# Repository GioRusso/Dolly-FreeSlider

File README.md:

# Dolly Free-Slider

Proyecto de grado - Ingeniería electrónica

Universidad del Norte - Barranquilla, Colombia

## Autores
* **Daniela Rada Estarita** - *Estudiante de pregrado* - destarita@uninorte.edu.co
* **Giorgio Russo Munarriz** - *Estudiante de pregrado* - grusso@uninorte.edu.co
* **Winston Percybrooks, Ph.D., M.Sc.** - *Ingeniero, asesor* - wpercyb@uninorte.edu.co
* **Norelli Schettini, Ph.D., M.Sc.** - *Ingeniera, asesora* - nschettini@uninorte.edu.co
* **Mauricio García, Magister** - *Diseñador Grafico, asesor* - garciamauricio@uninorte.edu.co

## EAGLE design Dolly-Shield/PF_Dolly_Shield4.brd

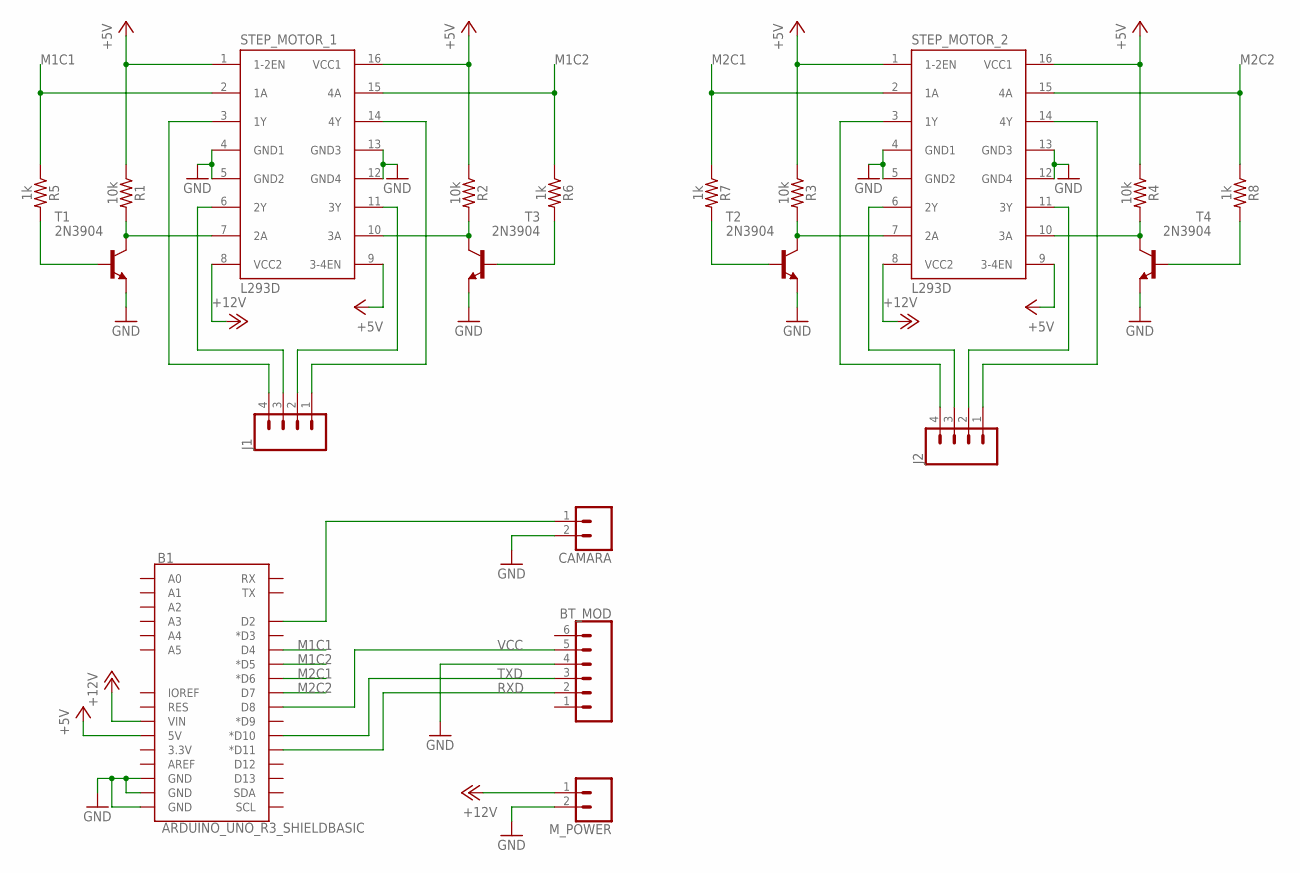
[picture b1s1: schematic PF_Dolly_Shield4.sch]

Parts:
B1: ARDUINO_UNO_R3_SHIELDBASIC; UNO_R3_SHIELD
BT_MOD: CONN_06LONGPADS; 1X06_LONGPADS
CAMARA: CONN_025MM; SCREWTERMINAL-5MM-2
J1, J2: CONN_04POLAR; MOLEX-1X4
M_POWER: CONN_025MM; SCREWTERMINAL-5MM-2
R1, R2, R3, R4: 10k; AXIAL-0.3
R5, R6, R7, R8: 1k; AXIAL-0.3
STEP_MOTOR_1, STEP_MOTOR_2: L293D; DIL16
T1, T2, T3, T4: 2N3904; TO92

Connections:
+5V: B1.5V, R1.P$1 (1), R2.P$1 (1), R3.P$1 (1), R4.P$1 (1), STEP_MOTOR_1.1 (1-2EN), STEP_MOTOR_1.9 (3-4EN), STEP_MOTOR_1.16 (VCC1), STEP_MOTOR_2.1 (1-2EN), STEP_MOTOR_2.9 (3-4EN), STEP_MOTOR_2.16 (VCC1)
+12V: B1.VIN, M_POWER.1, STEP_MOTOR_1.8 (VCC2), STEP_MOTOR_2.8 (VCC2)
GND: B1.GND@0 (GND), B1.GND@1 (GND), B1.GND@2 (GND), BT_MOD.4, CAMARA.2, M_POWER.2, STEP_MOTOR_1.4 (GND1), STEP_MOTOR_1.5 (GND2), STEP_MOTOR_1.12 (GND4), STEP_MOTOR_1.13 (GND3), STEP_MOTOR_2.4 (GND1), STEP_MOTOR_2.5 (GND2), STEP_MOTOR_2.12 (GND4), STEP_MOTOR_2.13 (GND3), T1.3 (E), T2.3 (E), T3.3 (E), T4.3 (E)
M1C1: B1.D4, R5.P$1 (1), STEP_MOTOR_1.2 (1A)
M1C2: B1.D5 (*D5), R6.P$1 (1), STEP_MOTOR_1.15 (4A)
M2C1: B1.D6 (*D6), R7.P$1 (1), STEP_MOTOR_2.2 (1A)
M2C2: B1.D7, R8.P$1 (1), STEP_MOTOR_2.15 (4A)
unnamed: J1.4, STEP_MOTOR_1.3 (1Y)
unnamed: J1.3, STEP_MOTOR_1.6 (2Y)
unnamed: J1.2, STEP_MOTOR_1.11 (3Y)
unnamed: J1.1, STEP_MOTOR_1.14 (4Y)
unnamed: J2.3, STEP_MOTOR_2.6 (2Y)
unnamed: J2.2, STEP_MOTOR_2.11 (3Y)
unnamed: J2.4, STEP_MOTOR_2.3 (1Y)
unnamed: J2.1, STEP_MOTOR_2.14 (4Y)
unnamed: R1.P$2 (2), STEP_MOTOR_1.7 (2A), T1.1 (C)
unnamed: R2.P$2 (2), STEP_MOTOR_1.10 (3A), T3.1 (C)
unnamed: R3.P$2 (2), STEP_MOTOR_2.7 (2A), T2.1 (C)
unnamed: R4.P$2 (2), STEP_MOTOR_2.10 (3A), T4.1 (C)
unnamed: R5.P$2 (2), T1.2 (B)
unnamed: R6.P$2 (2), T3.2 (B)
unnamed: R7.P$2 (2), T2.2 (B)
unnamed: R8.P$2 (2), T4.2 (B)
unnamed: B1.D2, CAMARA.1
RXD: B1.D11 (*D11), BT_MOD.2
TXD: B1.D10 (*D10), BT_MOD.3
VCC: B1.D8, BT_MOD.5

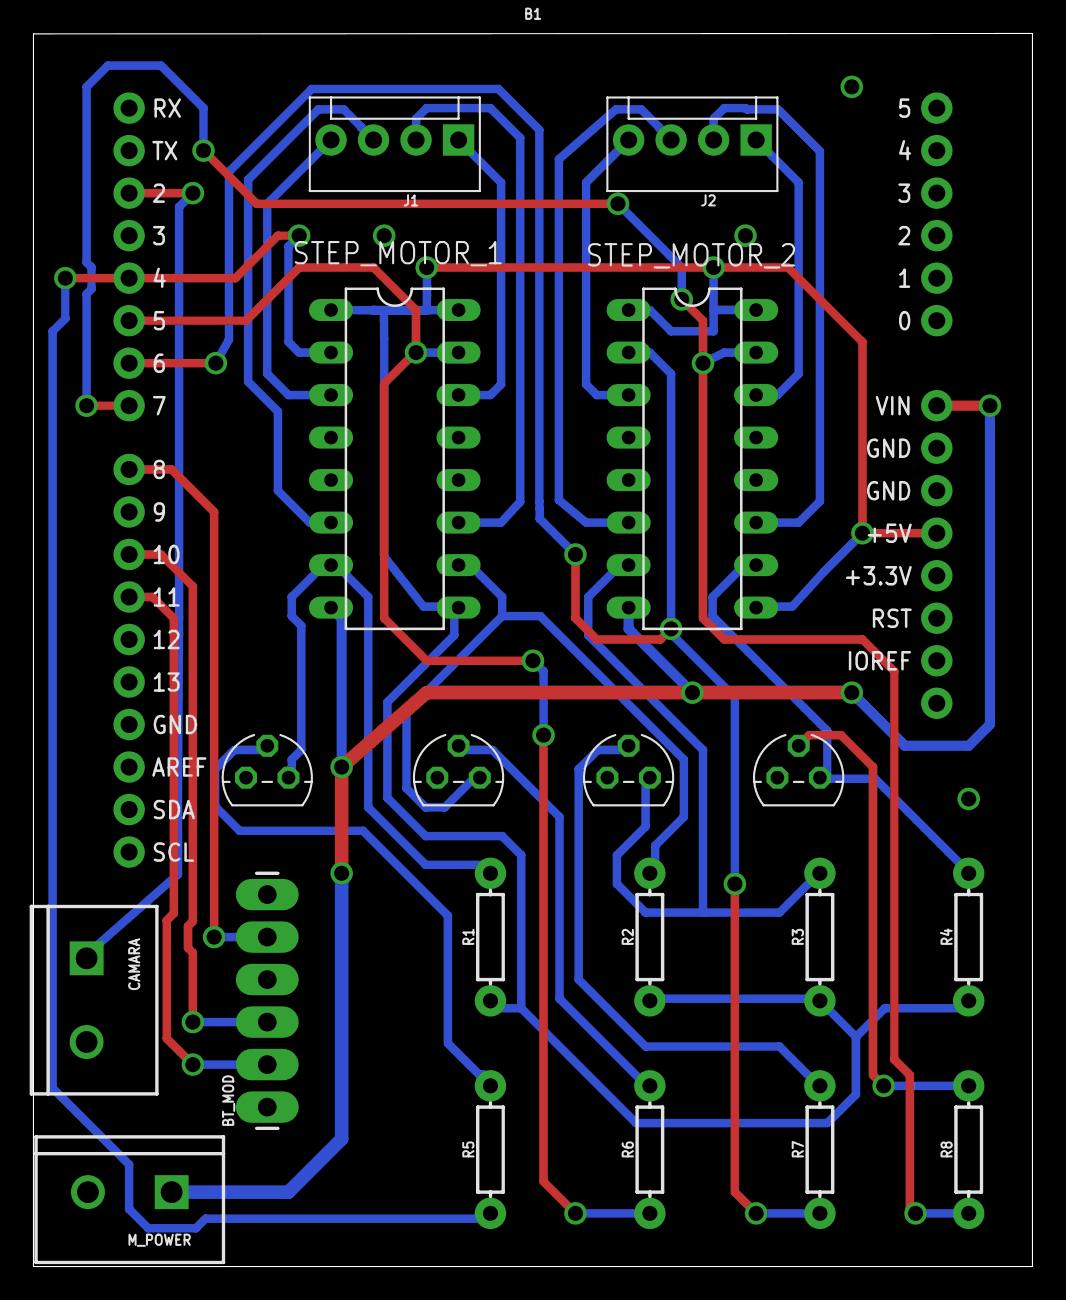
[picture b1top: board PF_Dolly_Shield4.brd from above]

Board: 2 copper layers, 59.7 x 73.7 mm, 20 parts (0 on the bottom side), 27 nets.

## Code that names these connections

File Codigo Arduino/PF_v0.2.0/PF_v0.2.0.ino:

#include <Stepper.h>

#define motorSteps 200
#define M1C1 4
#define M1C2 5
#define M2C1 6
#define M2C2 7
#define ledPin LED_BUILTIN

Stepper mDes(motorSteps,M1C1,M1C2);
Stepper mRot(motorSteps,M2C1,M2C2);  

void setup() {
  mDes.setSpeed(60);
  mRot.setSpeed(60);
  pinMode(ledPin, OUTPUT);
  blink(5);
}

void loop() {
  mDes.step(200);
  mRot.step(-200);
  blink(3);
  mDes.step(-200);
  mRot.step(200);
  blink(3);

}

// Blink the reset LED:
void blink(int howManyTimes) {
  int i;
  for (i=0; i< howManyTimes; i++) {
    digitalWrite(ledPin, HIGH);
    delay(200);
    digitalWrite(ledPin, LOW);
    delay(200);
  }
}

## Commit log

2017-11-07 Android exectuable
2017-11-08 Android App
2017-11-12 Codigo fuente micrtocontrolador ATmega328

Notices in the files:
parts and their libraries:
SparkFun-Boards: Licensing: Creative Commons ShareAlike 4.0 International - https://creativecommons.org/licenses/by-sa/4.0
